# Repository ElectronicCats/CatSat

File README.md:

# CatSat I

**[OSHW] MX0004 | Certified open source hardware |** [oshwa.org/cert.](https://www.oshwa.org/cert)

## Kit CatSat Education

Manual and more information in our [Wiki](https://github.com/ElectronicsCats/CatSat/wiki)

Electronic Cats invests time and resources providing this open source design, please support Electronic Cats and open-source hardware by purchasing products from Electronic Cats!

Designed by Electronic Cats.

Firmware released under an GNU AGPL v3.0 license. See the LICENSE file for more information.

Hardware released under an CERN Open Hardware Licence v1.2. See the LICENSE_HARDWARE file for more information.

Electronic Cats is a registered trademark, please do not use if you sell these PCBs.

16 July 2016

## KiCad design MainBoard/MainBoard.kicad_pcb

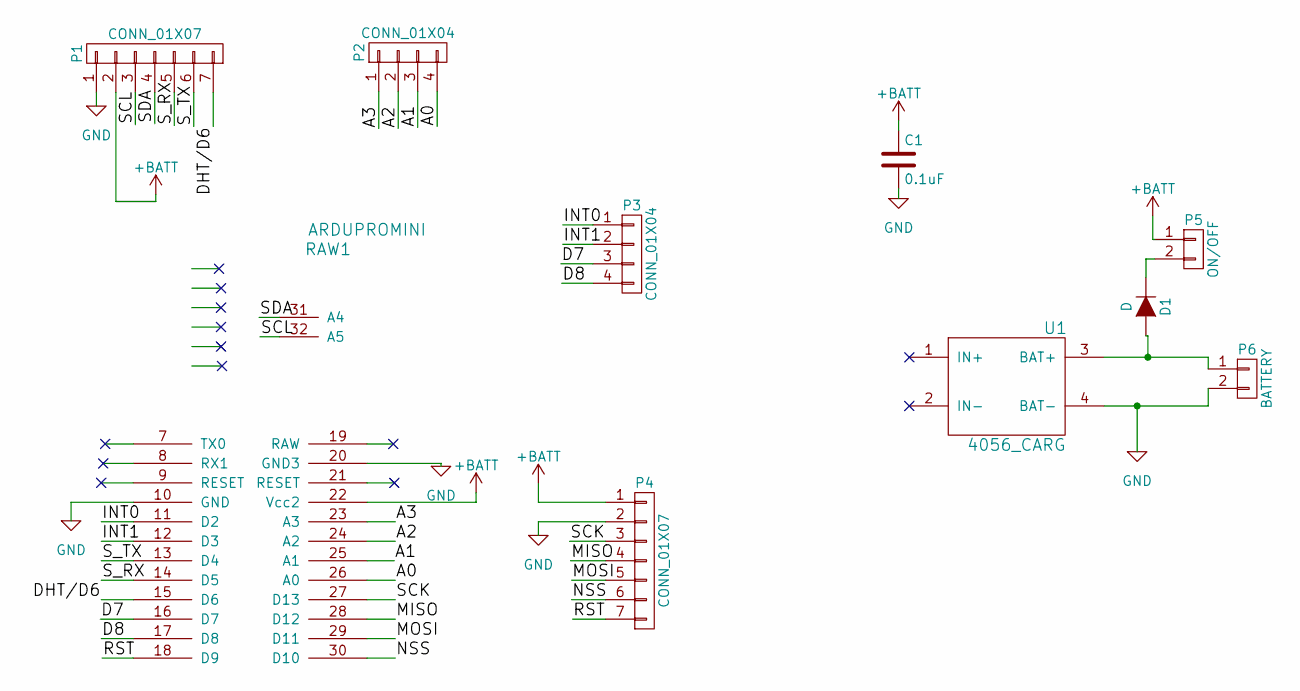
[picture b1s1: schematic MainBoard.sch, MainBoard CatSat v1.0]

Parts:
C1: 0.1uF; C_Disc_D6_P5
D1: D; Diode_DO-41_SOD81_Horizontal_RM10
P1, P4: CONN_01X07; Pin_Header_Straight_1x07
P2, P3: CONN_01X04; Pin_Header_Straight_1x04
P5: ON/OFF; Pin_Header_Angled_1x02
P6: BATTERY; Pin_Header_Straight_1x02
RAW1: ARDUPROMINI; arduinoMiniPro
U1: 4056_CARG; 4056_lipoCharg

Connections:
+BATT: C1.1, P1.2, P4.1, P5.1, RAW1.22 (Vcc2)
/A0: P2.4, RAW1.26 (A0)
/A1: P2.3, RAW1.25 (A1)
/A2: P2.2, RAW1.24 (A2)
/A3: P2.1, RAW1.23 (A3)
/D7: P3.3, RAW1.16 (D7)
/D8: P3.4, RAW1.17 (D8)
/DHT/D6: P1.7, RAW1.15 (D6)
/INT0: P3.1, RAW1.11 (D2)
/INT1: P3.2, RAW1.12 (D3)
/MISO: P4.4, RAW1.28 (D12)
/MOSI: P4.5, RAW1.29 (D11)
/NSS: P4.6, RAW1.30 (D10)
/RST: P4.7, RAW1.18 (D9)
/SCK: P4.3, RAW1.27 (D13)
/SCL: P1.3, RAW1.32 (A5)
/SDA: P1.4, RAW1.31 (A4)
/S_RX: P1.5, RAW1.14 (D5)
/S_TX: P1.6, RAW1.13 (D4)
GND: C1.2, P1.1, P4.2, P6.2, RAW1.10 (GND), RAW1.20 (GND3), U1.4 (BAT-)
unnamed: D1.1 (K), P5.2
unnamed: D1.2 (A), P6.1, U1.3 (BAT+)

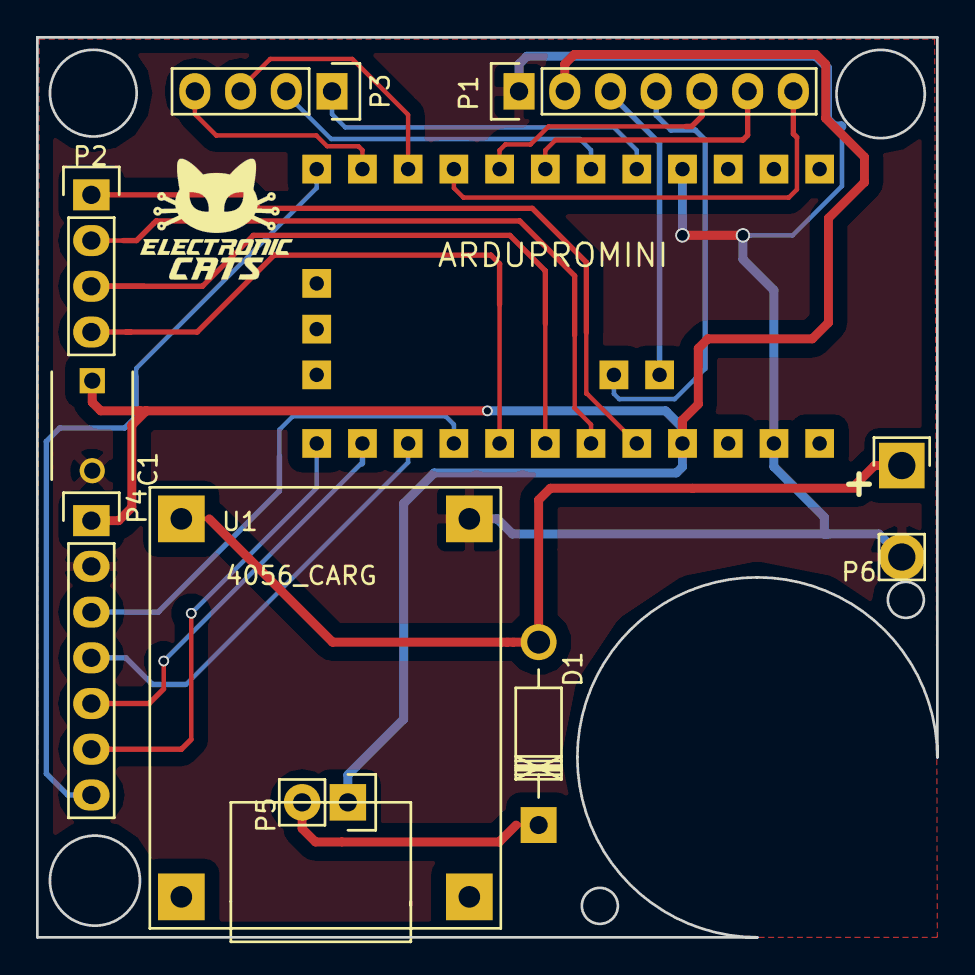
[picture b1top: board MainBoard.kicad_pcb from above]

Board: 2 copper layers, 50.0 x 50.0 mm, 10 parts (0 on the bottom side), 22 nets.

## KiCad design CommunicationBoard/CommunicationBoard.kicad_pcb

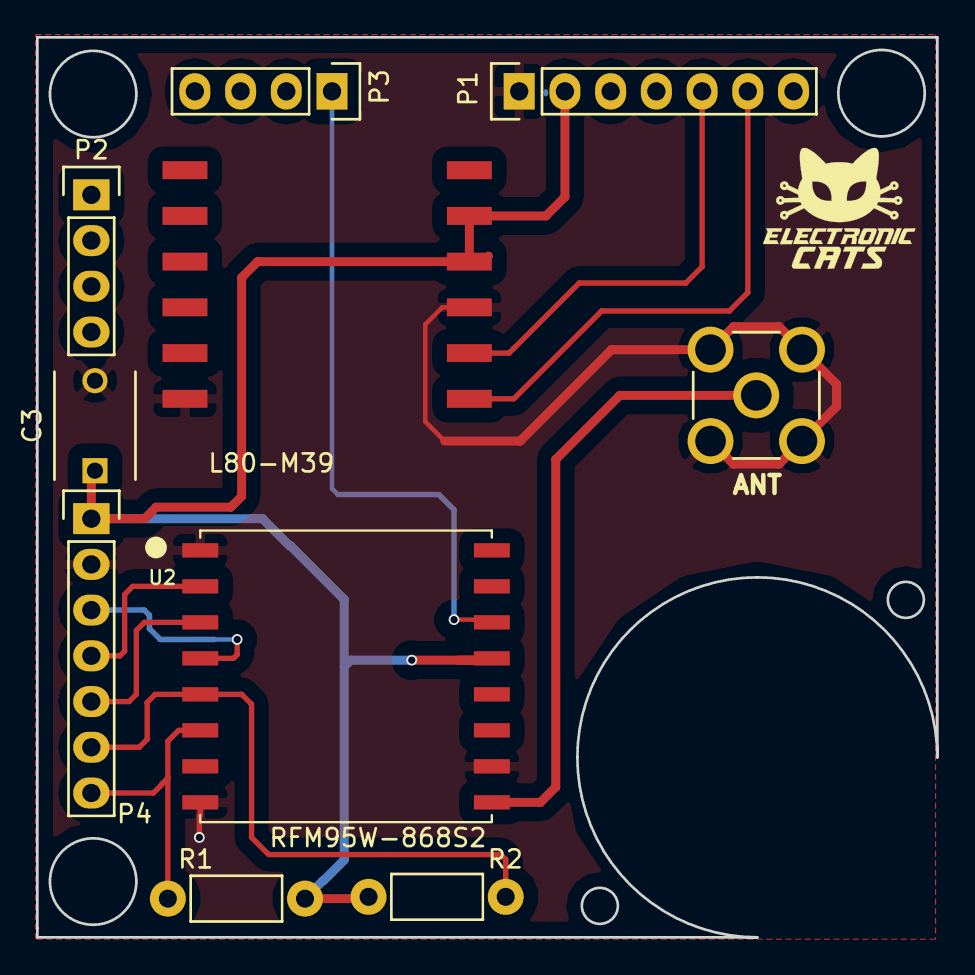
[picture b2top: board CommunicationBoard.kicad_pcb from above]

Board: 2 copper layers, 50.0 x 50.0 mm, 10 parts (0 on the bottom side), 11 nets.

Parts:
A1: ANT; AMPHENOL_901-144
C3: C; C_Disc_D6_P5
MODULE1: L80-M39; L80
P1, P4: CONN_01X07; Pin_Header_Straight_1x07
P2, P3: CONN_01X04; Pin_Header_Straight_1x04
R1, R2: R; Resistor_Horizontal_RM7mm
U2: RFM95W-868S2; RFM

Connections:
+BATT: C3.1, MODULE1.4, MODULE1.5, P1.2, P4.1, R1.1, R2.1, U2.13
GND: A1.2, A1.3, A1.4, A1.5, C3.2, MODULE1.3, MODULE1.12, P1.1, P4.2, U2.1, U2.8, U2.10
INT0: P3.1, U2.14
MISO: P4.4, U2.2
MOSI: P4.5, U2.3
NSS: P4.6, R2.2, U2.5
unnamed: A1.1, U2.9
RST: P4.7, R1.2, U2.6
SCK: P4.3, U2.4
S_RX: MODULE1.2, P1.5
S_TX: MODULE1.1, P1.6

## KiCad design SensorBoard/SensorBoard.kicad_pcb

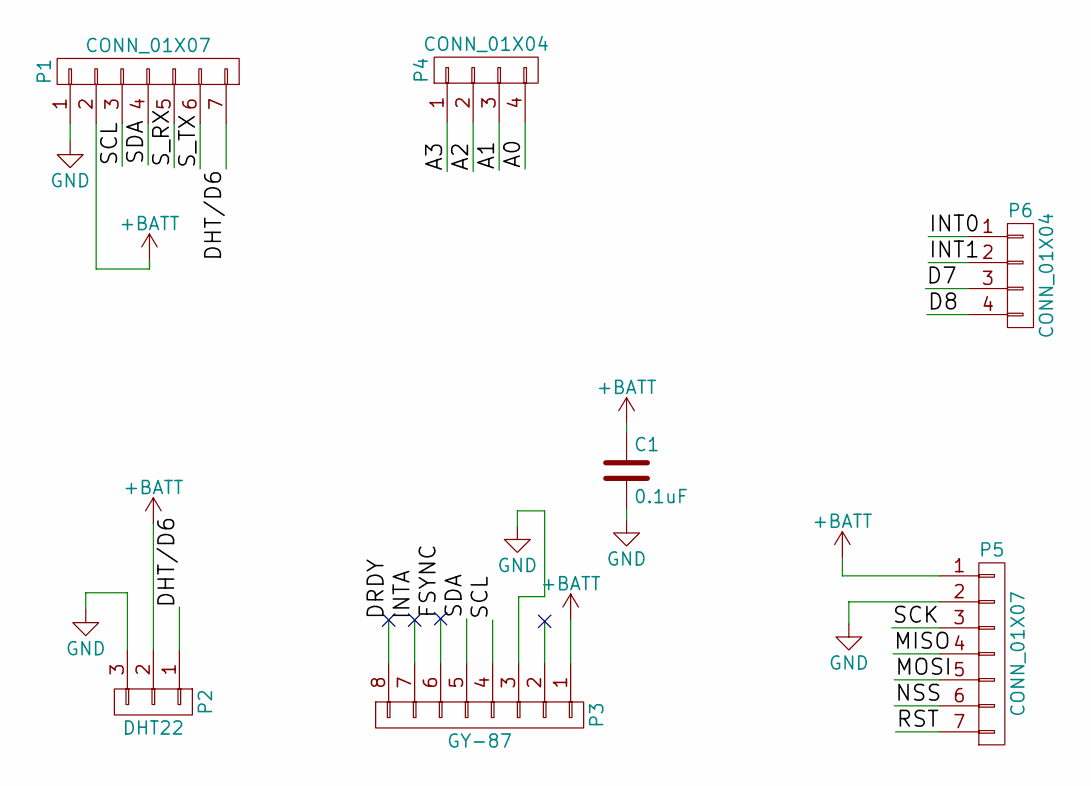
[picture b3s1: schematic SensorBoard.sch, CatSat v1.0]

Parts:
C1: 0.1uF; C_Disc_D6_P5
P1, P5: CONN_01X07; Pin_Header_Straight_1x07
P2: DHT22; Pin_Header_Straight_1x03
P3: GY-87; Pin_Header_Straight_1x08
P4, P6: CONN_01X04; Pin_Header_Straight_1x04

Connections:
+BATT: C1.1, P1.2, P2.2, P3.1, P5.1
/A0: P4.4
/A1: P4.3
/A2: P4.2
/A3: P4.1
/D7: P6.3
/D8: P6.4
/DHT/D6: P1.7, P2.1
/DRDY: P3.8
/FSYNC: P3.6
/INT0: P6.1
/INT1: P6.2
/INTA: P3.7
/MISO: P5.4
/MOSI: P5.5
/NSS: P5.6
/RST: P5.7
/SCK: P5.3
/SCL: P1.3, P3.4
/SDA: P1.4, P3.5
/S_RX: P1.5
/S_TX: P1.6
GND: C1.2, P1.1, P2.3, P3.3, P5.2

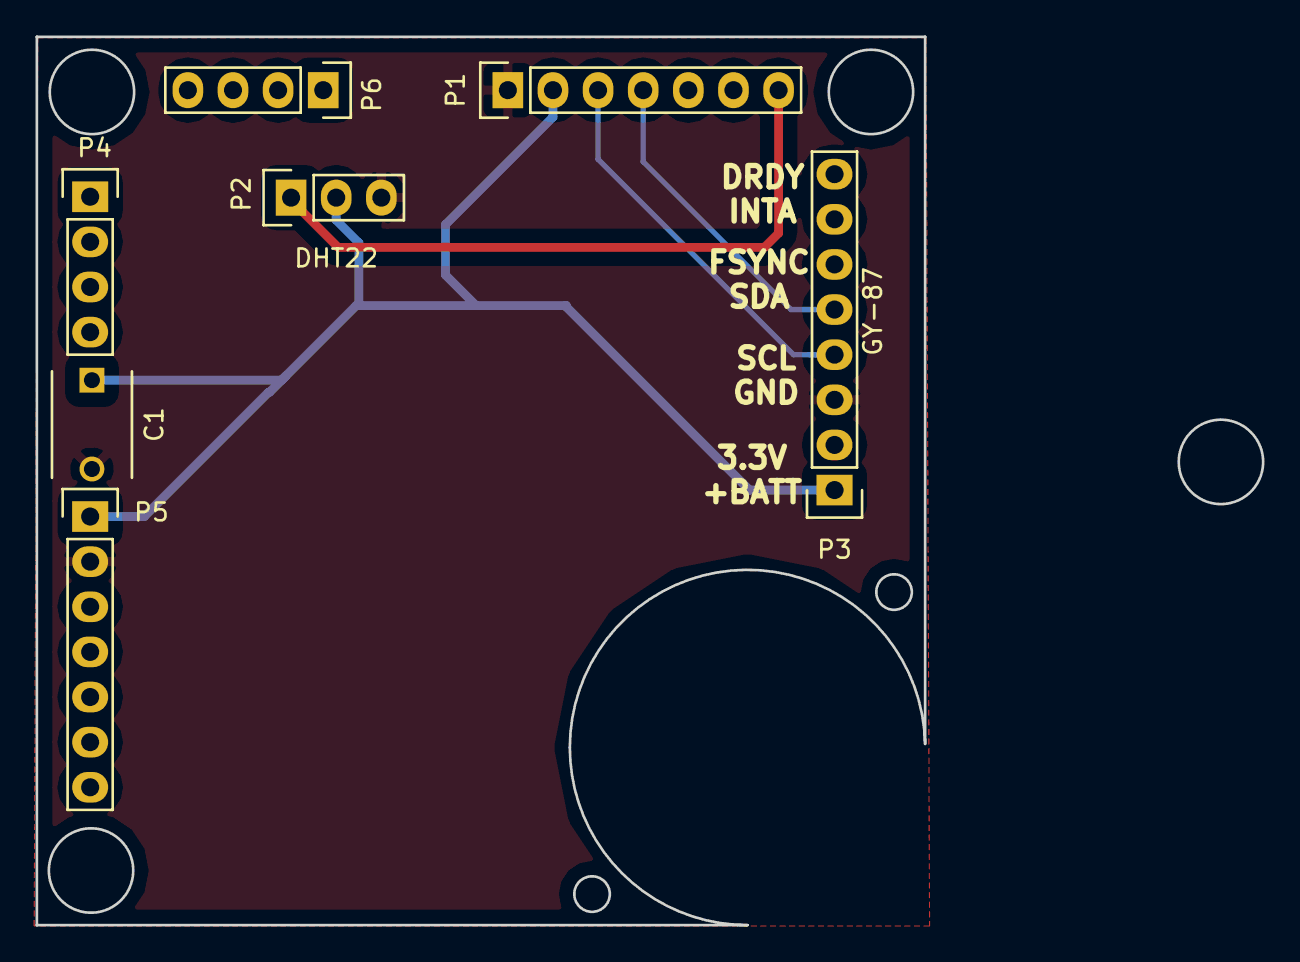
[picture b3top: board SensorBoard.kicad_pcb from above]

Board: 2 copper layers, 50.0 x 50.0 mm, 7 parts (0 on the bottom side), 5 nets.

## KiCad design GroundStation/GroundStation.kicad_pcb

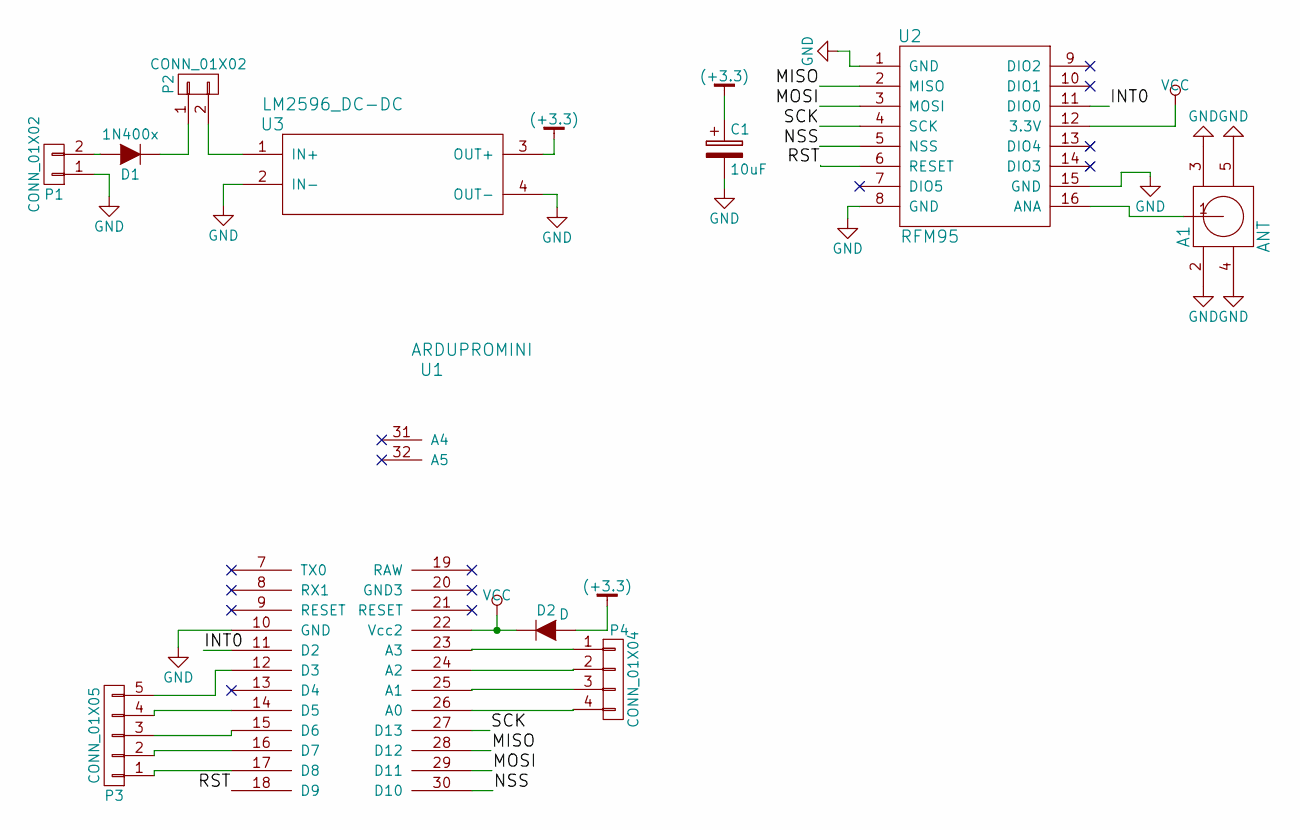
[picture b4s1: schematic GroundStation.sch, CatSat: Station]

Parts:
A1: ANT; AMPHENOL_901-144
C1: 10uF; C_Radial_D5_L6_P2.5
D1: 1N400x; Diode_DO-41_SOD81_Horizontal_RM10
D2: D; Diode_DO-41_SOD81_Horizontal_RM10
P1: CONN_01X02; bornier2
P2: CONN_01X02; Pin_Header_Straight_1x02
P3: CONN_01X05
P4: CONN_01X04
U1: ARDUPROMINI; arduinoMiniPro2
U2: RFM95; RFM
U3: LM2596_DC-DC; LM2596DC-DC

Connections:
(+3.3): C1.1, D2.2 (A), U3.3 (OUT+)
/INT0: U1.11 (D2), U2.11 (DIO0)
/MISO: U1.28 (D12), U2.2 (MISO)
/MOSI: U1.29 (D11), U2.3 (MOSI)
/NSS: U1.30 (D10), U2.5 (NSS)
/RST: U1.18 (D9), U2.6 (RESET)
/SCK: U1.27 (D13), U2.4 (SCK)
GND: A1.2, A1.3, A1.4, A1.5, C1.2, P1.1, U1.10 (GND), U2.1 (GND), U2.8 (GND), U2.15 (GND), U3.2 (IN-), U3.4 (OUT-)
unnamed: A1.1, U2.16 (ANA)
unnamed: D1.1 (K), P2.1
unnamed: D1.2 (A), P1.2
unnamed: P2.2, U3.1 (IN+)
unnamed: P3.1, U1.17 (D8)
unnamed: P3.2, U1.16 (D7)
unnamed: P3.3, U1.15 (D6)
unnamed: P3.4, U1.14 (D5)
unnamed: P3.5, U1.12 (D3)
unnamed: P4.1, U1.23 (A3)
unnamed: P4.2, U1.24 (A2)
unnamed: P4.3, U1.25 (A1)
unnamed: P4.4, U1.26 (A0)
VCC: D2.1 (K), U1.22 (Vcc2), U2.12 (3.3V)

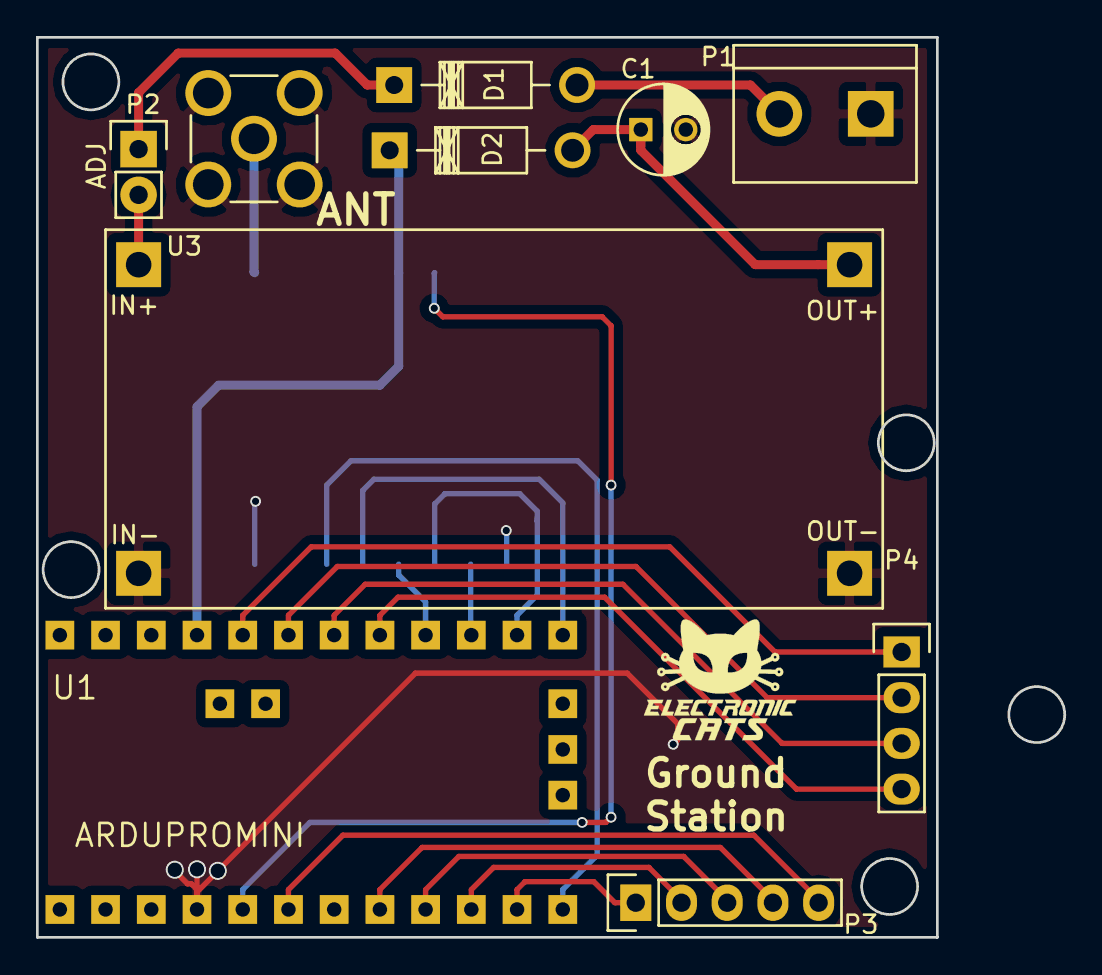
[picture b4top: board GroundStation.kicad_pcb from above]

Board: 2 copper layers, 50.0 x 50.0 mm, 11 parts (1 on the bottom side), 22 nets.

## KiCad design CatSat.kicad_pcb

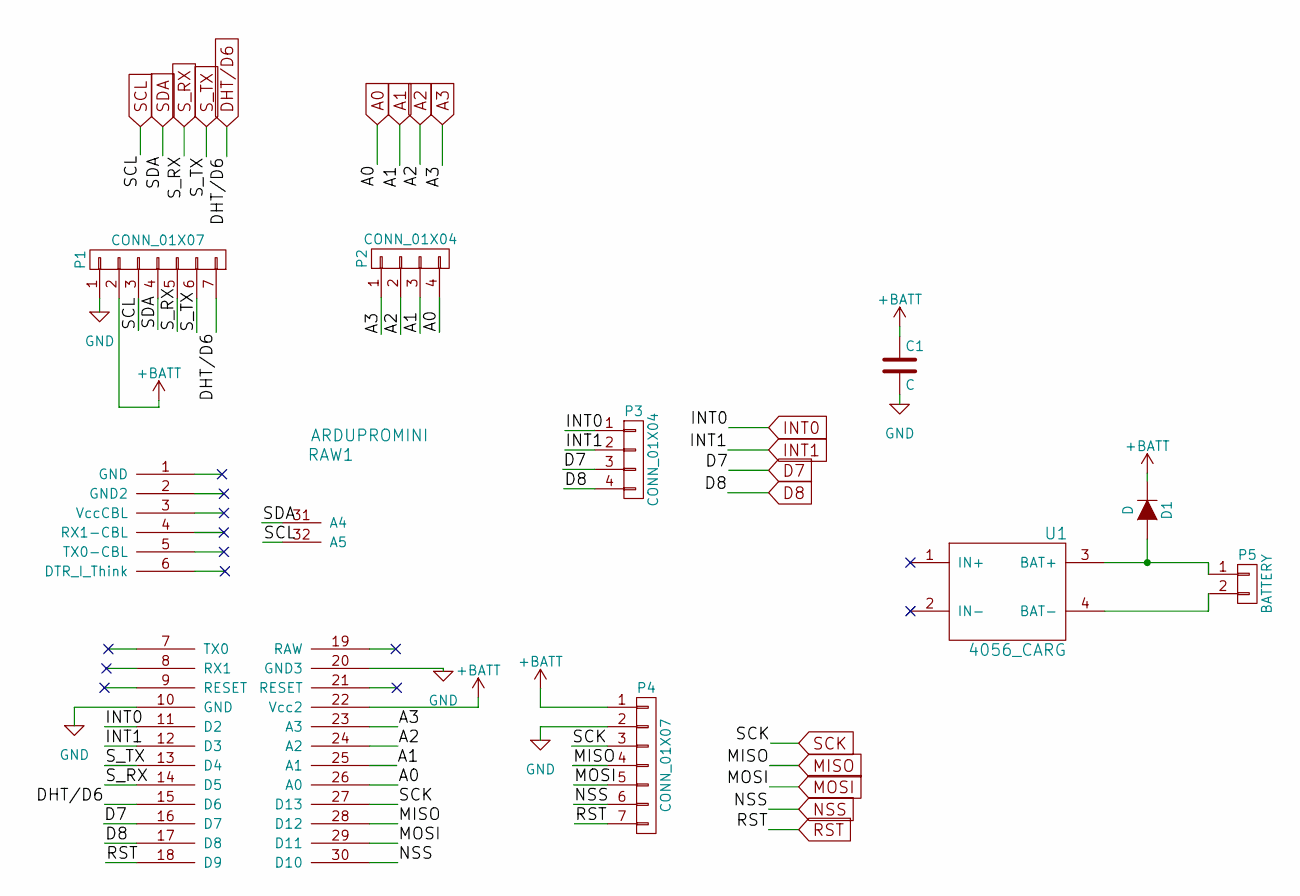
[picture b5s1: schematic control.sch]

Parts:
C1: C; C_Disc_D6_P5
D1: D; Diode_DO-41_SOD81_Horizontal_RM10
P1, P4: CONN_01X07; Pin_Header_Straight_1x07
P2, P3: CONN_01X04; Pin_Header_Straight_1x04
P5: BATTERY; Pin_Header_Straight_1x02
RAW1: ARDUPROMINI; arduinoMiniPro
U1: 4056_CARG; 4056_lipoCharg

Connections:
+BATT: C1.1, D1.1 (K), P1.2, P4.1, RAW1.22 (Vcc2); also elsewhere on the board
A0: P2.4, RAW1.26 (A0); also elsewhere on the board
A1: P2.3, RAW1.25 (A1); also elsewhere on the board
A2: P2.2, RAW1.24 (A2); also elsewhere on the board
A3: P2.1, RAW1.23 (A3); also elsewhere on the board
D7: P3.3, RAW1.16 (D7); also elsewhere on the board
D8: P3.4, RAW1.17 (D8); also elsewhere on the board
DHT/D6: P1.7, RAW1.15 (D6); also elsewhere on the board
INT0: P3.1, RAW1.11 (D2); also elsewhere on the board
INT1: P3.2, RAW1.12 (D3); also elsewhere on the board
MISO: P4.4, RAW1.28 (D12); also elsewhere on the board
MOSI: P4.5, RAW1.29 (D11); also elsewhere on the board
NSS: P4.6, RAW1.30 (D10); also elsewhere on the board
unnamed: D1.2 (A), P5.1, U1.3 (BAT+)
unnamed: P5.2, U1.4 (BAT-)
RST: P4.7, RAW1.18 (D9); also elsewhere on the board
SCK: P4.3, RAW1.27 (D13); also elsewhere on the board
SCL: P1.3, RAW1.32 (A5); also elsewhere on the board
SDA: P1.4, RAW1.31 (A4); also elsewhere on the board
S_RX: P1.5, RAW1.14 (D5); also elsewhere on the board
S_TX: P1.6, RAW1.13 (D4); also elsewhere on the board

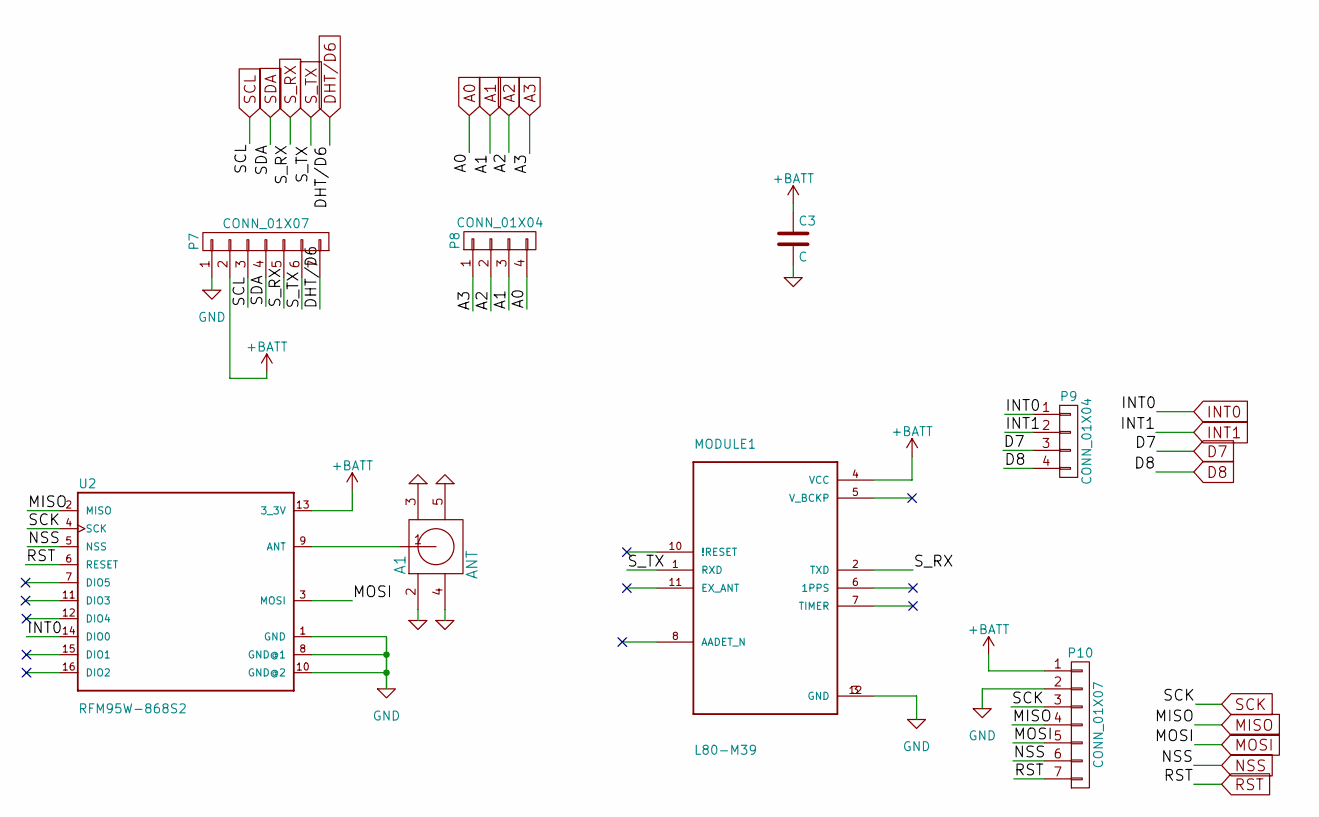
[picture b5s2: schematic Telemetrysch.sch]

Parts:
A1: ANT; SMA_Conn_Ant
C3: C; C_Disc_D6_P5
MODULE1: L80-M39; L80
P7, P10: CONN_01X07; Pin_Header_Straight_1x07
P8, P9: CONN_01X04; Pin_Header_Straight_1x04
U2: RFM95W-868S2; RFM

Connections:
+BATT: C3.1, MODULE1.4 (VCC), P7.2, P10.1, U2.13 (3_3V); also elsewhere on the board
A0: P8.4; also elsewhere on the board
A1: P8.3; also elsewhere on the board
A2: P8.2; also elsewhere on the board
A3: P8.1; also elsewhere on the board
D7: P9.3; also elsewhere on the board
D8: P9.4; also elsewhere on the board
DHT/D6: P7.7; also elsewhere on the board
INT0: P9.1, U2.14 (DIO0); also elsewhere on the board
INT1: P9.2; also elsewhere on the board
MISO: P10.4, U2.2 (MISO); also elsewhere on the board
MOSI: P10.5, U2.3 (MOSI); also elsewhere on the board
NSS: P10.6, U2.5 (NSS); also elsewhere on the board
RST: P10.7, U2.6 (RESET); also elsewhere on the board
SCK: P10.3, U2.4 (SCK); also elsewhere on the board
SCL: P7.3; also elsewhere on the board
SDA: P7.4; also elsewhere on the board
S_RX: MODULE1.2 (TXD), P7.5; also elsewhere on the board
S_TX: MODULE1.1 (RXD), P7.6; also elsewhere on the board

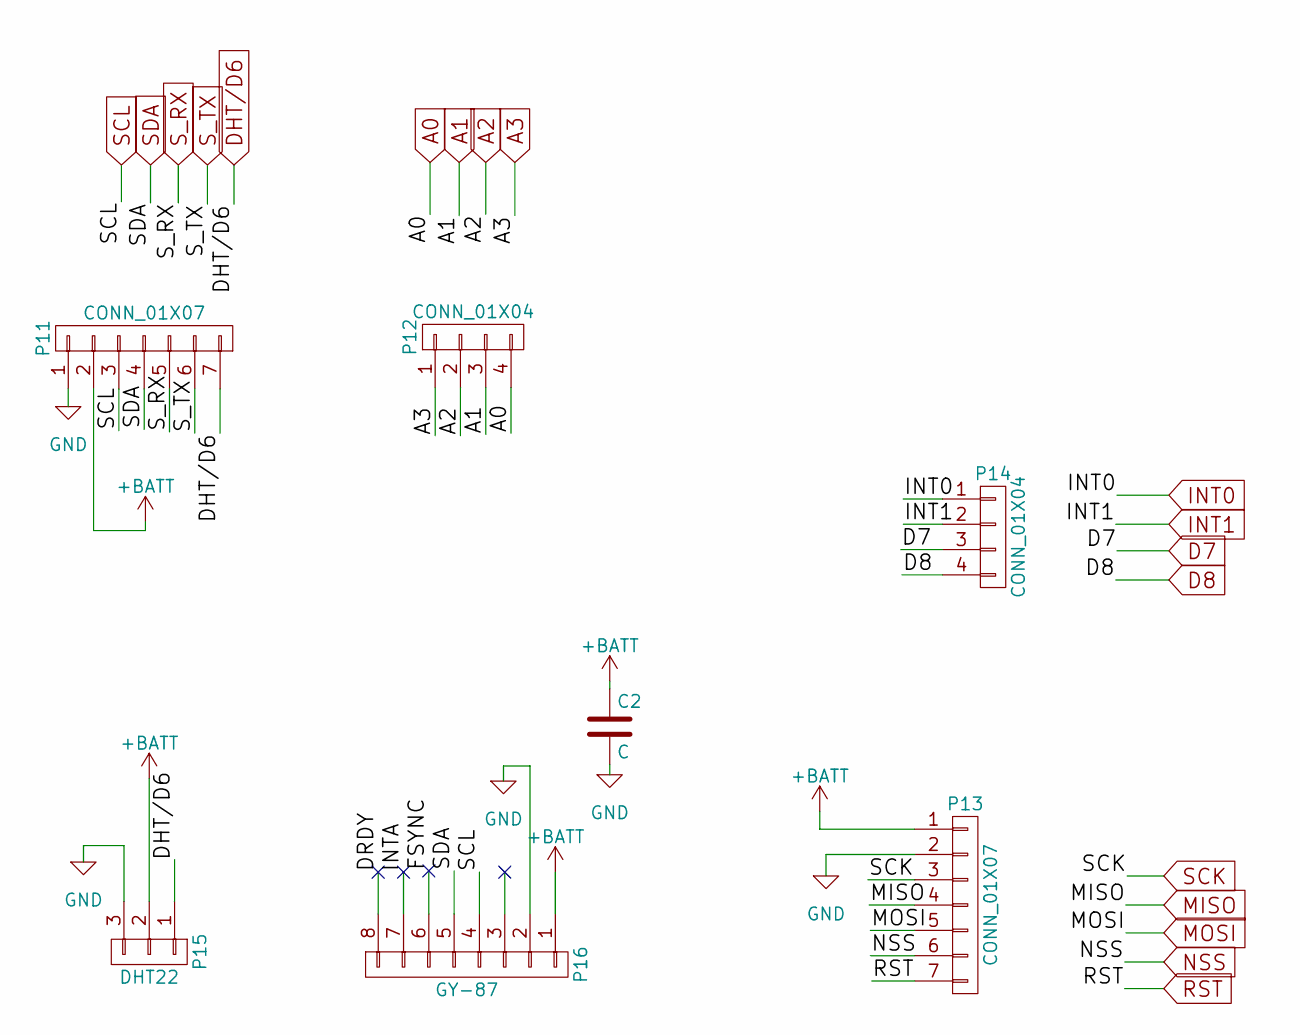
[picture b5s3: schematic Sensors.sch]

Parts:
C2: C
P11, P13: CONN_01X07; Pin_Header_Straight_1x07
P12, P14: CONN_01X04; Pin_Header_Straight_1x04
P15: DHT22; Pin_Header_Straight_1x03
P16: GY-87; Pin_Header_Straight_1x08

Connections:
+BATT: C2.1, P11.2, P13.1, P15.2, P16.1; also elsewhere on the board
/Sensors/DRDY: P16.8
/Sensors/FSYNC: P16.6
/Sensors/INTA: P16.7
A0: P12.4; also elsewhere on the board
A1: P12.3; also elsewhere on the board
A2: P12.2; also elsewhere on the board
A3: P12.1; also elsewhere on the board
D7: P14.3; also elsewhere on the board
D8: P14.4; also elsewhere on the board
DHT/D6: P11.7, P15.1; also elsewhere on the board
INT0: P14.1; also elsewhere on the board
INT1: P14.2; also elsewhere on the board
MISO: P13.4; also elsewhere on the board
MOSI: P13.5; also elsewhere on the board
NSS: P13.6; also elsewhere on the board
RST: P13.7; also elsewhere on the board
SCK: P13.3; also elsewhere on the board
SCL: P11.3, P16.4; also elsewhere on the board
SDA: P11.4, P16.5; also elsewhere on the board
S_RX: P11.5; also elsewhere on the board
S_TX: P11.6; also elsewhere on the board

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
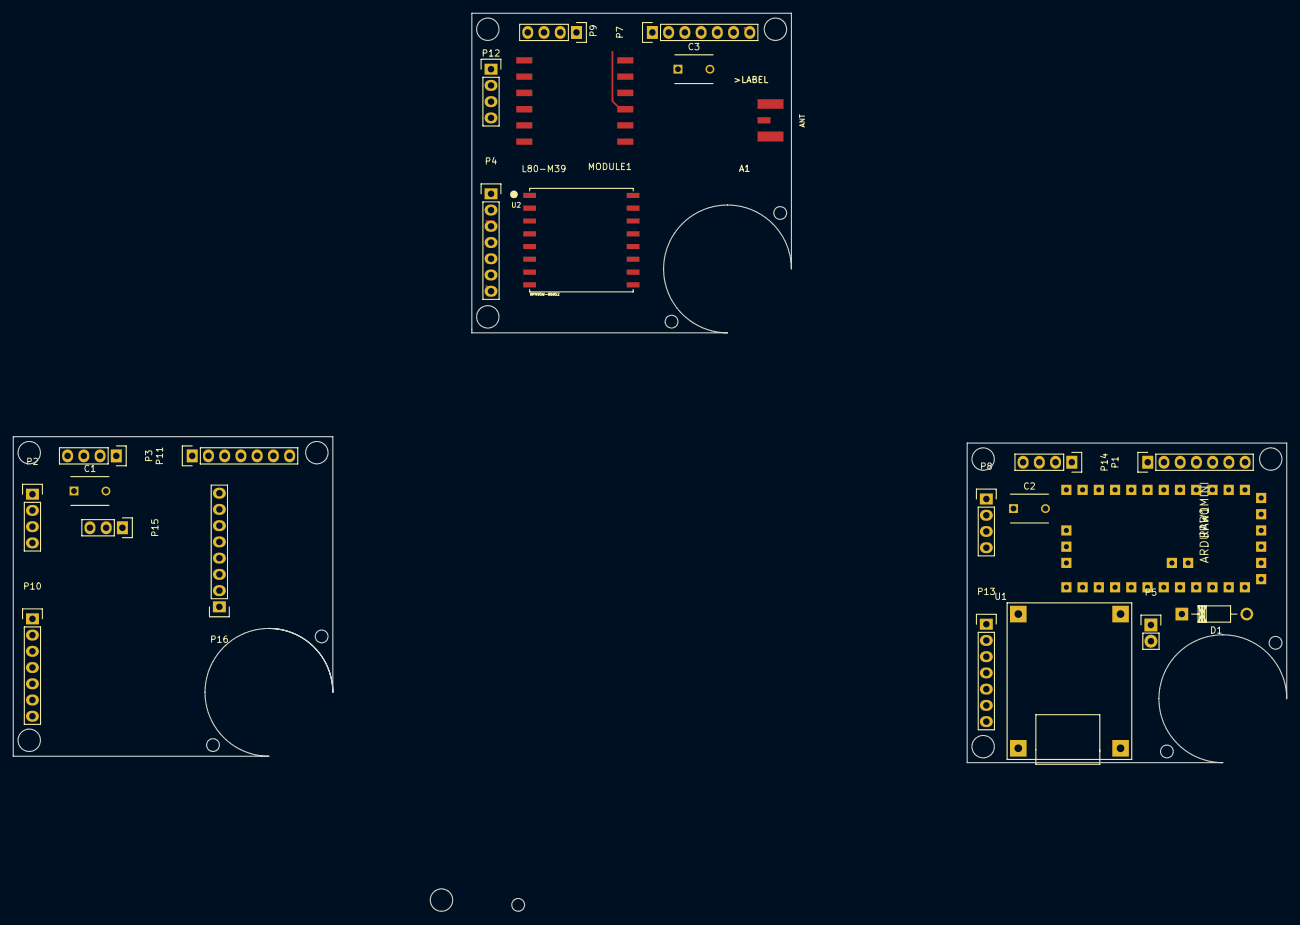
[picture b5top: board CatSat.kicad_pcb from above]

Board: 2 copper layers, 199.2 x 140.5 mm, 24 parts (0 on the bottom side), 23 nets.

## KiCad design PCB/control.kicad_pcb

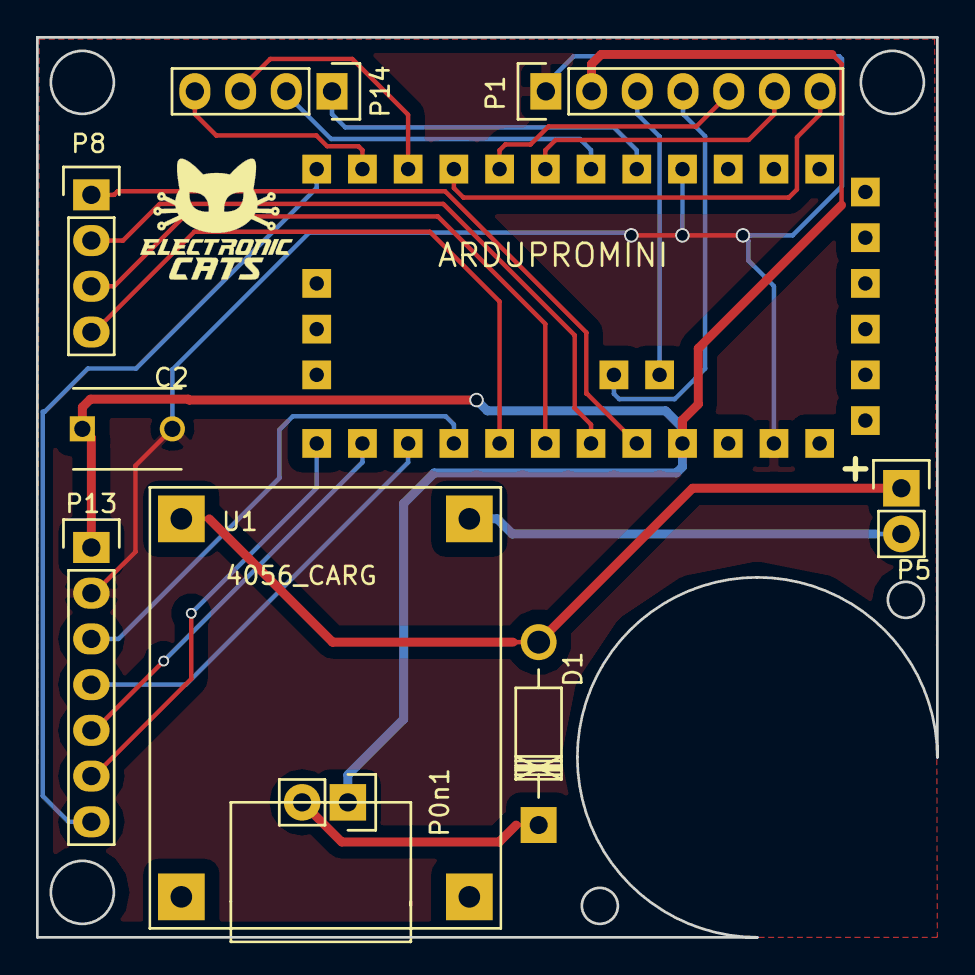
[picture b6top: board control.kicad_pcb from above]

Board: 2 copper layers, 50.0 x 50.0 mm, 10 parts (0 on the bottom side), 23 nets.

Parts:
C2: C; C_Disc_D6_P5
D1: D; Diode_DO-41_SOD81_Horizontal_RM10
P0n1: ON; Pin_Header_Straight_1x02
P1, P13: CONN_01X07; Pin_Header_Straight_1x07
P5: BATTERY; Pin_Header_Straight_1x02
P8, P14: CONN_01X04; Pin_Header_Straight_1x04
RAW1: ARDUPROMINI; arduinoMiniPro
U1: 4056_CARG; 4056_lipoCharg

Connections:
+BATT: C2.1, P0n1.1, P1.2, P13.1, RAW1.22
A0: P8.4, RAW1.26
A1: P8.3, RAW1.25
A2: P8.2, RAW1.24
A3: P8.1, RAW1.23
D7: P14.3, RAW1.16
D8: P14.4, RAW1.17
DHT/D6: P1.7, RAW1.15
GND: C2.2, P1.1, P13.2, RAW1.10, RAW1.20
INT0: P14.1, RAW1.11
INT1: P14.2, RAW1.12
MISO: P13.4, RAW1.28
MOSI: P13.5, RAW1.29
NSS: P13.6, RAW1.30
unnamed: D1.1, P0n1.2
unnamed: D1.2, P5.1, U1.3
unnamed: P5.2, U1.4
RST: P13.7, RAW1.18
SCK: P13.3, RAW1.27
SCL: P1.3, RAW1.32
SDA: P1.4, RAW1.31
S_RX: P1.5, RAW1.14
S_TX: P1.6, RAW1.13

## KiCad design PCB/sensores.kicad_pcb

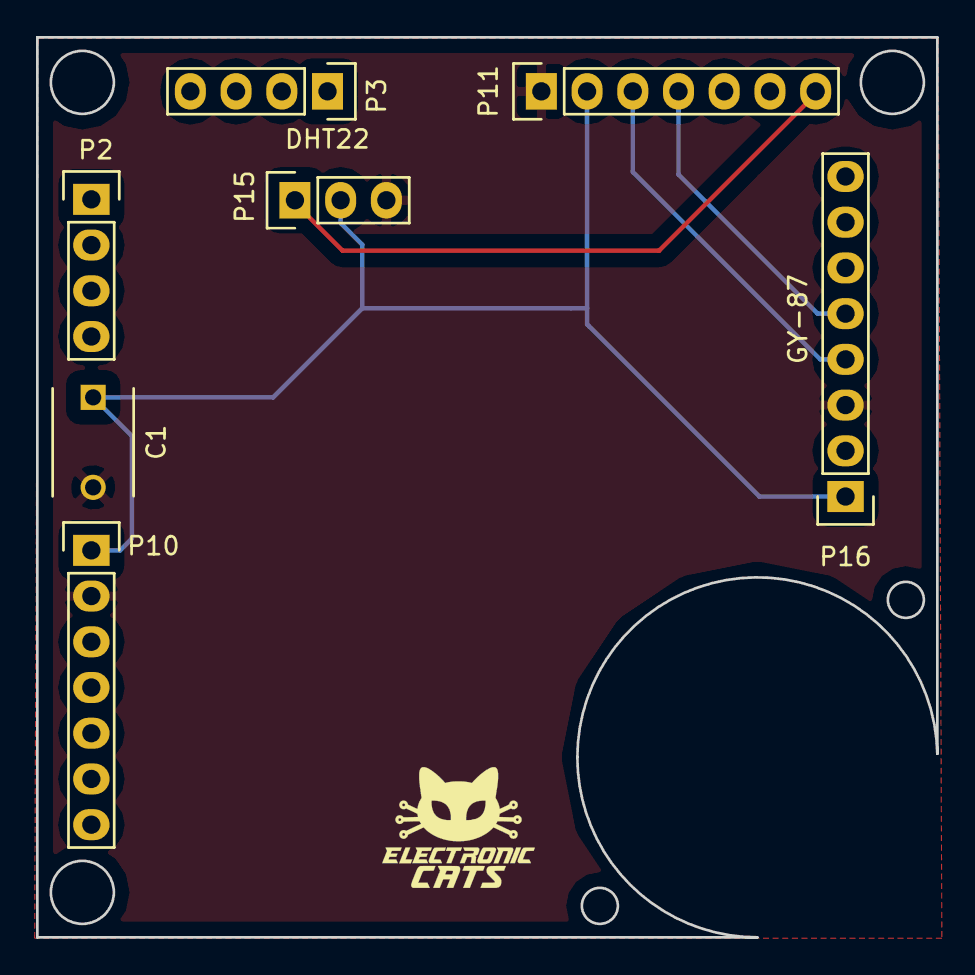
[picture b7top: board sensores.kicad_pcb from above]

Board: 2 copper layers, 50.0 x 50.0 mm, 7 parts (0 on the bottom side), 5 nets.

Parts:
C1: C; C_Disc_D6_P5
P2, P3: CONN_01X04; Pin_Header_Straight_1x04
P10, P11: CONN_01X07; Pin_Header_Straight_1x07
P15: DHT22; Pin_Header_Straight_1x03
P16: GY-87; Pin_Header_Straight_1x08

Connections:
+BATT: C1.1, P10.1, P11.2, P15.2, P16.1
DHT/D6: P11.7, P15.1
GND: C1.2, P10.2, P11.1, P15.3, P16.3
SCL: P11.3, P16.4
SDA: P11.4, P16.5

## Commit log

2016-07-18 First version firmware BPM180,HMC and DHT22
2016-07-18 Add Licences
2016-07-18 Add code HCM5883L
2016-07-19 adding MPU6050 to CatSat
2016-07-19 add tinygps
2016-07-19 add tinygps full
2016-07-19 Fix code
2016-07-19 Add F PROGMEM
2016-07-19 Commented prints unnecessary
2016-07-21 Added LoRa communications
2016-07-22 fix comment and add library Lora link
2016-07-22 Added string with raw data and send
2016-07-25 Added Schematic
    Initial Schematic in KiCad
2016-07-27 Schematic v0.2
    Added IC and wiring
2016-07-27 Added gitignore
2016-07-29 Fix arduino mini pro pin 6 bug, added capacitors
2016-07-29 Added PCB's
2016-07-29 Added library with footprints
2016-07-29 gitignore re-added
2016-07-29 gitignore correct
2016-07-31 Change Tiny GPS to TinyGPSPlus
2016-08-01 Finished telemtry PCB
2016-08-01 Fix PCBs
2016-08-01 Fix PCB sensores
2016-08-01 Add logo ElectronicCats
2016-08-01 Fix bug GND of GY-87
2016-08-02 PCB final
2016-08-02 Added earth station
2016-08-03 Fix details
2016-08-03 Add logos
2016-08-03 Fix sma connector and pads
2016-08-04 Update logos and fix pads
2016-08-06 Earth_station v1.2
2016-08-07 Temporary solution GPS
2016-08-10 Fix earth station and ID to the frimware
2016-08-11 Add images
2016-08-11 Added schematic PDF
2016-08-11 Update README
    License hardware
2016-08-11 Fix Source Track
2016-08-11 Update DHT Pin
2016-08-12 added logo to schematic
2016-08-20 Earth_station Fix
    Capacitor changed
2016-08-23 Added Logos
2016-08-25 Fix tracks and vias width
2016-08-25 Added holes
2016-08-26 Fix Wire
2016-08-27 Fix design 0.2V
2016-08-27 Fix 0.3v
2016-08-27 Move Logos
2016-08-27 Via fix again
2016-08-27 Toc Fix Ignacio
2016-08-27 String edit with ","
2016-09-03 Add PDF's
2016-09-03 Fix string for parse
2016-09-03 Fix dht error
2016-09-03 note ID node
2016-09-03 Add EarthStation firmware
2016-09-07 Fix string again again
2016-09-07 Fix paths
2016-09-07 Added PDF reference
2016-09-13 Added Manual Camera
2016-09-13 Update gitignore
2016-09-15 Added datasheet RFM95
2016-10-08 fix string
2016-10-08 Fix bug double raw
2016-10-16 Rename EarthStation to GroundStation
2016-10-16 Move Path Footprint
2016-10-16 New Path Communication
2016-10-16 New path MainBoard
2016-10-16 New Path Sensor Board
2016-10-16 BackOldversion Path and name boards
2016-10-16 Remove folder PCBs
2016-10-16 Update Schematic MainBoard
2016-10-16 Update Schematic SensorBoard
2016-10-16 Update Schemcatic Communication
2016-10-16 Update Names in Schematic
2016-10-16 Update README with Wiki Link
2016-10-16 Update referencePCB for schematic MainBoard
2016-10-16 Update PCB referenceschematic SensorBoard
2016-10-16 Update PCB with Schematic
2016-10-18 Update PCB footprints MainBoard
2016-10-18 Update PCB via Sensor Board
2016-10-18 Update PCB via GPS & Telecomm board
2016-10-18 Correction pad, via and logo
2016-10-18 fix via data dht22
2016-10-18 Fix Ground station <3
2016-10-18 Add label's Communication board
2016-10-18 Added labels pinout SensorBoard
2016-10-18 Add 1.1v
2016-10-18 Fix GroundStation Firmware
    Rename File and folder
2016-10-18 Added label Main Board
2016-10-18 Fix Label Communication
2016-10-18 Add extra I/O pins Ground station
2016-10-18 Fix Labels GroundStation
2016-10-18 Added Schematic PDFs
2016-10-18 Added images of boards
2016-10-25 Correction Main Board
2016-10-25 Correction GroundBoard
2016-11-15 Fix Bugs
2016-12-15 Correction tracks
2016-12-29 Add larger holes
2017-01-05 Remove pines FTDI Arduino mini
2017-04-25 Available in Tindie!
2017-06-06 add LM2596 to kicad
2017-06-06 Added altitude and velocity for GPS
2017-06-08 Update datasheet GPS L80
2017-06-08 Test command balloon mode
2017-06-16 Add RSSI on Groundstation and channel selection
2018-01-17 Add SF12
2018-01-17 Add RSSI
2018-01-17 Add channel configuration
2018-01-17 Add comments
2018-01-17 Add balloon mode
2018-08-15 Add logo certified as open source
2018-08-15 Add logo OSHW
2018-08-15 Fix Typo
2018-10-02 Add new payload
    Added folder for new payload and project
2018-10-26 add footprint
2018-10-27 Keep cleaning
2018-10-31 Update payload
2019-01-16 migrate to NEGPS library
2019-01-16 change to arduino lora
2019-01-16 set pins rfm95
2019-01-16 ground station migrate
2019-01-16 remove comments
2019-01-17 Change select band function
2019-01-17 Migrate to NEOGPS and LoRa Arduino
2019-01-17 Update timing on sending data
2019-01-17 best comments
2019-01-17 best traslate
2019-01-17 new library reference
2019-01-17 change led to builtin
2019-01-18 update version arduino
2019-01-18 remove variables comment
2019-01-18 best commment of line
2019-01-18 Rename sketch CatSat1
2019-01-18 add NeoSWSerial
2019-01-18 remove variable not used
2019-01-24 define debug
2019-01-25 Update name
2019-01-25 Rename folder
2019-01-25 add altitude and speed
2019-01-25 Add Accelerometer function
2019-01-26 fix gps without gps flag, remove temporal millis function
2019-01-27 revert commit comment mag.getevent
2019-01-27 new nmea command
2019-01-27 revert comment
2019-01-28 Add altitude and velocity by GPS
2019-01-28 update raw txt
2019-01-28 Fix bug lora frequency
2019-01-28 erase \n to add the RSSi at ground station
2019-01-30 Change type of altitude
2019-02-12 Add Case for 3D printing
2019-02-26 fix mode gps ballon
2019-02-26 remove repet ballon mode
2019-02-28 add detect gps and command ballon
2019-03-05 erase tx interval
2019-03-05 Patch magnetometer library error
2019-03-05 Change selectBand function
2019-03-05 Add firmware version
